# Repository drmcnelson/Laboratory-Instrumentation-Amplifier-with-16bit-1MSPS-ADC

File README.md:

# Laboratory Instrumentation Amplifier with bipolar inputs, 16bit 1MSPS ADC, SPI for Teensy, Arduino

By [Dr M. C. Nelson](https://github.com/drmcnelson/Laboratory-Instrumentation-Amplifier-with-16bit-1MSPS-ADC),  [Copyright 2020-2026](LICENSE)

> **Important Build Note:** To ensure performance and alignment with the validated hardware and firmware, please build only from the **[Original Repository](https://github.com/drmcnelson/Laboratory-Instrumentation-Amplifier-with-16bit-1MSPS-ADC)**. 
>
>  For technical assistance or commercial inquiries, please contact me. I do my best to answer emails as volume allows.
<br>

---
### Table of contents
[Introduction](#intro)<br>
[1. Contents and instructions](#repo)<br>
[2. Design details](#design)<br>
[3. Spice model](#spice)<br>
[4. ADC sampling and timing](#timing)<br>
[5. Detailed part selection](#parts)<br>
[6. PCBWay sponsorship and acknowledgement](#ack)<br>

---
<br>

## Introduction

Instrumentation amplifiers ("INAs") are important for making sensitive precise stable voltage measurements with very high input impedance and strong noise rejection.
If you do research in the physical sciences or engineering or study electrical phenomena in biological systems, then you have probably used an INA.
They are a cornerstone of traditional instruments such as electrometers, and EKG machines, and laboratory studies in chemical physics, semiconductors, advanced materials, organo- and bio- electronics.

But, if you have used a traditional INA in your research, you may have noticed that they have certain limitations (which we are going to address in this design).
In particular, there is a well known trade-off where precision or sensitivity comes at the expense of some combination of bandwidth and impedance.
INAs are typically low bandwidth devices.
But there are interesting phenomena, for example involving charge processes on microsecond time scales, where high impedance measurements with a fast INA would be an especially useful tool.

This limitation in traditional INAs arises, at least in part, in two properties of amplifier chips; the input voltage noise density e<sub>n</sub> (V/√Hz) and the input current noise density i<sub>n</sub> (A/√Hz).
At a given bandwidth and impedance these contribute to the noise as *v*<sub>e,rms</sub> ≈ e<sub>n</sub>√f and *v*<sub>i,rms</sub> ≈ z<sub>n</sub> i<sub>n</sub> √f.
Note that both have a factor of root frequency but the current noise density is also multiplied by impedance.
We can think of a "noise resistance", R<sub>n</sub> = e<sub>n</sub>/i<sub>n</sub>.
When the amplifier input sees an impedance larger than R<sub>n</sub>, current noise dominates and noise increases more rapidly with bandwidth.
Low noise with high impedance and bandwidth requires low noise density with high noise resistance, alongside adequate bandwidth and slew.

Let's illustrate this with a numerical example. If we want 16 bit data for a signal of 1V, the noise (rms) should be around 10μV or smaller.
For a bandwidth of 1MHz, we need e<sub>n</sub> ≈ 10nV/√Hz.
And for an impedance of 10Mohm, we need i<sub>n</sub>  ≈ 1fA/√Hz.
That is, we need current noise density in the range of single digit fA/√Hz, or smaller.
It is challenging to find what we need in older INA chips (see [Table 5.8 in H&H AOE 3rd ed.](https://archive.org/details/the-art-of-electronics-3rd-ed-2015_202008/page/363/mode/1up)),
But there *are* newer Op Amps with ~10nV/√Hz and ~1fA/√Hz noise densities, >MHZ bandwidth and >10V/μs slew.
So, this is where a "roll your own" approach can be an advantage over older INA chips.

Another issue in traditional INAs is that they most often have single ended outputs.
The modern paradigm in high performance analog to digital converters (ADC) is increasingly to have differential inputs.
And, there is a large repertoire of high performance fully differential amplifiers (FDA) designed specifically to drive these differential ADCs.
Rather than run a single ended BNC across the lab to an analog input in a crate, nowadays we interface our high performance analog circuit over a short differential path to a high performance ADC co-located on the same board and export an all digital interface to an inexpensive microcontroller board or a computer.
The analog noise is well managed within a small area of the circuit board, and an all differential signal path helps control noise all the way to the ADC with its digital interface.

### About the INA and other contents of this repository:

In this repository we provide cad files and software source codes to make and operate an up-to-date instrumentation amplifier (INA) that can accommodate 10Mohm impedances with 16 bit precision at 1MSPS.
The host interface is a simple convert (CNVST) signal and SPI.
Asserting the "CNVST" line initiates conversion to digital and
after 700 nsecs, with CNVST low, a 16 bit SPI transfer retrieves the data.
The logic level for the SPI and CNVST are per the Vdd pin in the external connector and can be between 1.7V to 5.5V.
The SPI can be clocked as fast as 100MHz.
The INA board must be powered at -5V and +5V.
We provide a dual power supply for this, which we describe later.

We include an Arduino "sketch" (as source code) to operate the INA from a Teensy or Arduino microcontroller (MCU) board, and a Python program to provide an interactive interface to operate the instrument and record and display data in real time from a desktop or laptop computer.
The MCU board appears as a serial device to the computer with human readable commands and responses.
The source code has been compiled for and run on a Teensy 4, an Arduino UNO R4 and a STM32 Nucleo 144 (F7).
We prefer the Teensy for having the best SPI implementation and the fastest USB.

As described below, the basic operation of the device is simple and it should be easy to customize or crib from the source code or python code to integrate the INA into your experiment.

In the following we include some discussion of the design process, especially as related to part selection.
And we provide spice models that may help you check your changes, if you want to make any changes to the design.

For a more thorough discussion of the electrical topics mentioned here, the reader is referred to Horowitz, P., & Hill, W. (2015). The art of electronics (3rd ed.). Cambridge University Press. ISBN-10 0521809266.  Especially see Chapter 5 "Precision Circuits" and Chapter 8 "Low Noise Techniques".

### A word on the Spi Instrumentation Project:

Building instruments is an old tradition in science.  Many of the great advances were by scientists working with instrument makers or who were themselves great instrument makers.  In recent decades there is a different kind of pressure on academic science.  There seems to be less time or interest for learning those kinds of skills, compared to writing proposals to buy equipment.
Consequently doing science has become much more expensive and the sort of science someone gets to do increasingly becomes a function of where they are.
But like many things in nature, science is cyclic, and scientists are resourceful.
With the advent of low cost high performance MCU boards, 3-d printers and low cost CNC machines, there is now a growing community in DIY lab equipment.
But, there is still a roadblock when it comes to some of the more advanced design challenges.
Few are able to build a photon tagging system with picosecond timing from scratch, for example.
Our contribution, as long time instrumentation physicists is to fill in the gap to make higher end capabilities available to this new paradigm.
We believe that combining high end instrumentation circuits with the new generation in Arduino type MCU boards can be a powerful tool that can bring important capabilities to your lab and contribute to truly open science.

There is a sponsor button at the top of this repository.  Please do consider joining with us and contributing to our effort.

### Our sponsor for the INA - [PCBWay](https://www.pcbway.com/) 

We want to express special appreciation to PCBWay for sponsoring assembly of the first INA boards.  I enjoyed working them and we plan to work with PCBWay going forward.  Going back to PCBWay for the next designs and contributing to their community project forum, really is the best kind of praise that I can muster for any vendor.

On that note, we plan to post this design to the PCBWay community forum as our first experiment in this paradigm.  We are eager to see how it works out.

### Obtaining boards:

To obtain boards, the options include ordering a board through PCBWay per the above, or contact me and then click the sponsor button.
The parts cost at Digikey is USD 36 per board at this writing.
Preparing an order still takes a few hours of careful attention since we review everything and check for updates in the BOM each time.
<br>

<br>

---

## 1. Contents and Instructions:
In this repo you will find:
<ol type="a">
<li>
KiCad files - for a high performance INA with a 16 bit 1 MSPS ADC that can be used with a Teensy 4.x, UNO R4, Nucleo144 or other Arduino type MCU board.
</li>
<li>
Source code - to operate the INA with any of the above platforms to record voltages and waveforms in single, averaged, clocked or triggered data acquisition modes, implement a set of human readable commands and transfer data over USB.
</li>
<li>
Python code - class library and utility program that runs on a desktop or laptop to operate the INA-MCU, view data in realtime and save data to disk files.
</li>
<li>
SPICE models - in LTSpice for the complete circuit and including a model for the ADC.
</li>
</ol>

### a) Fabrication
In the KiCAD files directory you will find a zip file with gerbers, drill and placement files, and a BOM.  These are easily regenerated from the KiCAD files.  If you are not familiar with ordering PCBs or assembly, the support team at PCBWay will guide you through the process.  Alternatively, you can sponsor a fabrication run and get a board.  Contact me for more information about this.

### b) Controllers
You may want to use the INA with one of our controllers.
Please see our new [Teensy 4.0 based controller here (rev3)](https://github.com/drmcnelson/Instrumentation-Controller-T4.0-Rev3) 
and our [T4.1 based controller here](https://github.com/drmcnelson/SPI-Instrumentation-Controller-T4.1).
We recommend these over other Arduino type MCU boards because of (a) the faster processor, (b) faster USB, (c) native 16 bit transfer capability already built into the Teensy SPI library, and (d) managed power.

### c) Power requirements and recommended power supply
The INA requires a -5V,+5V power supply.
The repo for our [+/-5V instrument power supply is  here](https://github.com/drmcnelson/Dual-pos-neg-5V-Supply-from-USB-power)
The power architecture of the INA assumes the the board is powered by this power supply.
The power supply in turn is normally powered from the filtered +5V power connector provided on the controller although it can alternatively be powered directly from USB

### d) The complete setup with controller and recommended power supply.
The following shows a complete setup with the INA, T4 based controller and power supply.  Notice the power supply is powered by the +5V connector on the controller and then powers the INA.   The INA is connected to the controller by a 12 pin (2x6) ribbon cable.

Here we show the input connectors. The instrumentation amplifier can be used as a single ended or differential input.  Input impedance is jumper selected as will be discussed.

### e) Input range and bandwidth
The range at each side of the differential input is -4V to +4V.
Full scale for the differential signal is therefore 8V.
Spectral response is flat from DC.
There is a low pass filter with time constant at the Nyquist limit for the 1MHz sample rate.

### f) Increasing gain
Gain can be increased by adding the resistor Rg.
There is a thru-hole footprint for this part located between the input header and the first Op Amp chip.
The gain equation is G = 1/2 + 10K/Rg.
Rg = 100 will give you a gain of 100.5.
With a gain of 100, the full scale range on each side of the differential input is effectively 40mV and the full scale differential signal is 80mV.
Larger inputs will clip since the rails for the Op Amps are just a little past -4V and +4V.

### g) Jumpers, selecting input impedance
There are three pin jumpers adjacent to each side of the differential input.
These allow you to select a 10M or 100K shunt to ground.
With no jumper installed the input impedance is that of the non-inverting input of the Op Amp.
It is important to have some path to ground, whether it is through the shunt resistor or the sample, rather than leave the input to drift off to one of the rails.

### h) Thermistor and measurements with voltage divider
You might use the internal 100K shunt with an external 100K thermistor to make accurate temperature measurements, or with an external resistor to form a divider to look at larger voltages.

The setup with a thermistor would look like the following where Vin is a known constant voltage and the internal resistor is selected by the jumpers as described above.  The controller has a high precision voltage reference output that you can use for this.

The setup with a divider would look similar to the above, though the external resistance might be considerably larger.
If you use a divider to measure large voltages, be very careful that the resulting voltage at the divider is within 4V.

Keep in mind also that Johnson (thermal) noise density for a resistor is about 0.13√R in units of nV/√Hz.
For a 16 bit precision on ±4V, 1LSB corresponds to 122μV. 
For 1Mohm and 1MHz the Johnson noise is 130uV.
So a 10:1 divider using the internal 100K and a 900K external can be okay.
With larger resistors more bits are used up for noise.
<br>

### i) Specs
<table style="width:60%;margin-left:30px">

<th>
Specifications
</th>
<tr>
<td style="padding-left:1rem">
 Input range
</td>
<td>
±4V each (±8V differential)
</td>
</tr>

<tr>
<td style="padding-left:1rem">
Input Impedance
</td>
<td>
10M, 100K, 1T (open), 20pF
</td>
</tr>

<tr>
<td style="padding-left:1rem">
Sampling rate
</td>
<td>
1 MSPS
</td>
</tr>

<tr>
<td style="padding-left:1rem">
Precision
</td>
<td>
16 bit
</td>
</tr>

<tr>
<td style="padding-left:1rem">
Digital Noise
</td>
<td>
+/-1 LSB
</td>
</tr>

<tr>
<td style="padding-left:1rem">
External Interface
</td>
<td>
CNVST, SPI to 100MHz, VDD 1.7V to 5.5V
</td>
</tr>

<tr>
<td style="padding-left:1rem">
Analog Power
</td>
<td>
-5V, +5V
</td>
</tr>
</table>

<br>
<br>

---

## 2. Design details

### a) Architecture

The traditional INA architecture is shown in the following diagram.
The input stage is a pair of Op Amps tied together by the resistor network R1-Rg-R1. The second stage is a difference amplifier with single ended output.
The overall gain is G = (1 + 2R1/Rg)(R3/R2).
This is a well studied circuit, you can read about it
in the textbook by Horowitz and Hill cited in the introduction,
or at [Wikipedia](https://en.wikipedia.org/wiki/Instrumentation_amplifier)
or in the many vendor application notes on the subject.

<p align="center">

<br>
<caption>
INA in the traditional configuration has single ended output.
</caption>
</p>

The following circuit diagram shows the INA architecture that we want to use for our circuit.
The differential amplifier is replaced with a fully differential amplifier (FDA) and the output from the FDA is interfaced to the differential input of a high performance ADC.
The ADC communicates with the outside world, for example a Teensy board or Arduino, over SPI.

<p align="center">

<br>
<caption>
INA with differential output stage and differential ADC.
</caption>
</p>

### b) Component selection, in brief

For our Op Amp selection, key parameters include the input current noise density i<sub>n</sub>, input voltage noise density e<sub>n</sub>, slew rate, and power supply rejection ratio (PSRR) as follows:
<ul>
<li>
Voltage noise density should be in the range of nV/√Hz for 16 bit precision with 1MHz bandwidth.
</li>
<li>
Current noise density in the range of single digit fA/√Hz is a pre-requisite for 16 bit precision with order 10 Mohm input impedance and 1 MHz bandwidth.
</li>
<li>
Slew rate in the range of 10V/us or better is a requirement for being able to study phenomena that appear as steps or transients on a μs time scale.
</li>
<li>
Power supply rejection ratio above 60dB is a requirement for the Op Amp and for the FDA, with the recommended power supply.  This is discussed later in further detail for the ADC.
</li>
</ul>

For the design provided here, the input stage is an ADA4510-2,  which is a dual Op Amp with i<sub>n</sub> = 4fA/√Hz, e<sub>n</sub> ≈ 5nV/√Hz, maximum slew = 19V/μs and PSRR 140dB.
As noted above, at 10Mohms at 1MHz, our noise is 40uV.

For the FDA, all of the above are important except that the current noise requirement is relaxed since the FDA sees low source impedances in the outputs from the first stage.  We choose an LT1994, which exceeds the front end specs with e<sub>n</sub> ≈ 3nV/√Hz and slew at 85V/μs.  Its PSRR is 105dB.

Both the ADA4510 and LT1994 are rail to rail parts.

For the ADC, our requirements include 16bits, 1MSPS, differential inputs, reference voltage, input range to 4V on each side of the differential input, SPI for the interface to the MCU, and it should accommodate 3.3V or 5V logic levels to be able to interface to a wide range of Arduino boards.  The precision and speed puts us in the range of a SAR type ADC.
The flexibility in logic levels narrows the selection somewhat.
It is also important to closely check performance specs including latency, missing codes, SNR, INL and DNL.

In this design we choose the Microchip MCP33131D as a 16 bit differential input 1MSPS SAR type ADC with SPI that can accommodate the required logic levels.
The SNR is listed as 91.3 dB which translates to a noise level of about 1 LSB.
This is one spec where the corresponding TI part might seem marginally better, but it comes at the cost of only accepting 3.3V logic.

For a voltage reference we select the REF3440 which has 3.8uV/V noise, low dropout at 100mV and is recommended for 16bit to 18bit ADCs.

### c) Interfacing to the ADC

SAR type ADCs, like most analog input architectures, feature a switched sampling capacitor.
A simplified version is as follows.
The switch closes connecting the input to the sampling capacitor.
The resistor represents the overall resistance inside the input including the closed resistance of the switch.
The capacitor then charges to the voltage at the input.
The switch opens and the SAR reads the voltage and converts it to a digital representation.

There are two interrelated challenges in driving a switched capacitor network; providing a charge reservoir for the in-rush current when the switch closes, and assuring that the capacitor charges quickly enough or that there is sufficient time in the sampling window, for the sampling capacitor to come within 1 LSB of the input voltage.
The recommended strategy is to provide a charge reservoir in the form of an external capacitor, and a buffer amplifier to charge the reservoir, as follows.

The trick in the above, is that these two capacitors charge on different time scales.
The sampling time allowed for charging the internal sampling capacitor is usually smaller than the period between samples.
The buffer has to supply current on the slower time scale to keep the reservoir charged, but it is the reservoir that absorbs the large fast spike when the switch closes.
   
The design process for the interface to the ADC is then:
   1) Choose the external capacitor to be a few times larger than the internal capacitor, then
   2) Choose the external resistor so that the time constant is faster than 1/2 of the sampling rate, and then
   3) Choose an Op Amp that is (a) able to deliver current equal to the full scale voltage divided by the external resistor, and (b) has a maximum slew that is much larger than the full scale voltage divided by the sampling period.
 
 With that high level view, let's take a look at our ADC.

The datasheet for the MCP33131D ADC provides the following equivalent circuit for its input.

Here we see a switched capacitor network for each side of the differential input.
There seems to be a novelty in that the sampling circuit is represented with a second switch to isolate the capacitor between samples.
Manufacturers often describe the state of the sampling capacitor as "unknown" between sampling events.
Here the intent seems to be a little more specific.
But in actuality there has to be some loss of charge between sampling events even if very small.

In practice, when you model a switched sampling capacitor network in SPICE, you always include a second switch to discharge the capacitor between samples.
If your driving circuit will get the sampling cap to the right voltage within the sampling window coming from 0 each time, it should be okay when you deploy it in the actual device.

Meanwhile, we have some important takeaways from the equivalent circuit.
The capacitor sees a time constant of 6.2 nanoseconds provided there is minimal impedance seen in the driving circuit, and we need something much larger than 30pf in the external capacitor.

---

## 3. SPICE model

For purposes of designing and modeling a circuit to drive an ADC, standard practice as mentioned above, is to use a model similar to the following for the switched sampling capacitor network:

In other words for purposes of modeling the sampling input, we discharge the capacitor between samples. 
A circuit that can drive the sampling cap from 0 to within 1LSB of the input voltage within the sampling period, should be sufficient for any reasonable state of the cap in operation.

The following shows our INA circuit with the equivalent circuit for the sampling input from the datasheet for the ADC.
External to the ADC, on each of the inputs, we have a resistor and capacitor to act as a charge reservoir for the sampling capacitor.
Internal to the ADC sample and hold, we have the switches as shown in the equivalent circuit from the datasheet.
Recall that this ADC isolates the capacitor between sampling windows.

<figure>
<p align="center">

<br>
<caption>
INA circuit model for SPICE,
</caption>
</p>
</figure>

The following shows (a) the voltages at the positive and negative inputs of the two front end amplifiers in two shades of green, and (b) the voltages at the two outputs of the FDA in two shades of blue.
As required for the ADC, the inputs are transformed from a bipolar range from -4V to +4V, to a unipolar range from 0V to 4V.

<p align="center">

<br>
<caption>
Voltages at inputs to the front end (green) and at the output
s of the FDA (red and lavender).
</caption>
</p>

The following shows (a) the output from one side of the FDA (blue), (b) the voltage on the sampling capacitor (red), (c) switching clock for the sampling network (grey).
We see that voltage on the sampling capacitor easily tracks the input to the ADC.

<figure>

<br>
<figcaption>
Positive side output from the FDA (blue), voltage on the sampling capacitor (red), and sampling clock (grey).
</figcaption>
</figure>

Here we add traces for the current through the sampling cap (green) and the capacitor services as the external charge reservoir (gold).
Notice the current spike through the sampling capacitor.
We see this is supplied by the external capacitor acting as charge reservoir, which slowly charges between switch events.
Notice also that there is no discernible spike in the output from the FDA.
So the charge reservoir is working as it is supposed.
On each sampling cycle, the sampling capacitor is able to rapidly come to the voltage presented at the input.

<figure>

<br>
<figcaption>
Positive side output from the FDA (blue), voltage on the sampling capacitor (red), current through the sampling capacitor (green), current through the external reservoir capacitor (gold) and the sampling clock (grey).
</figcaption>
</figure>

It is good practice to always check your ADC designs this way.  Find the equivalent circuit in the datasheet and implement it in terms of the capacitances and resistances and make sure you are driving it correctly.

Now, we have two more very important aspects of our circuit design to check, spectral response and noise.
We will look at these at the input to the ADC.
For completeness the following is our SPICE model modified for these analyses with large source impedance on each side of the differential input.

<figure>

<figcaption align="center">
Spice model with large source impedances.
</figcaption>
</figure>

The following shows the spectral analysis.  If you do not know how to do this in LTSpice, there is [a short tutorial video here](https://youtu.be/fziUQaVQxA4?feature=shared)
Here we see that our response is flat to 100kHz and then rolls off only slowly reaching -1.4dB and a 45 degree phase shift at around 1MHz.
If you want a more aggressive roll off you can substitute the caps in the feedback networks in the front end, or use larger caps for the charge reservoir in front of the ADC.

<figure>

<figcaption align="center">
Spectral response.
</figcaption>
</figure>

The following shows the noise analysis. As above, you can [see how to do this in LTSpice in the short tutorial video here](https://youtu.be/hBsBl27etYs?feature=shared).
https://youtu.be/hBsBl27etYs?feature=shared
 The noise density remains well below our target for 16 bit precision throughout the entire spectral range, even with a 1M source impedance at the input.

<figure>

<figcaption align="center">
Noise density.
</figcaption>
</figure>

So, it appears that the design meets our goals,  We expect to be able to make 16 bit 1MSPS measurements with high source impedance.
Spectral response is flat and then rolls off by less than 2dB above 100KHz and noise is under our 120uV requirement throughout the spectral range.

---

## 4. ADC Sampling and Timing

Voltage sampling is controlled by the CNVST pin in the double row header.  Assertion of this pin effectively marks the end of the sampling interval, causes the most recent level at the input to be converted to digital and made available for retrieval by the host.  The timing relationship between CNVST and the sampling window is important if the ADC sampling is to be synchronized to another instrument or specific external events.

The ADC, a MCP33131D-10, is described in detail in the datasheet found [here](https://ww1.microchip.com/downloads/en/DeviceDoc/MCP33131D-Data-Sheet-DS20005947B.pdf).
Figure 6-10, page 37, reproduced below, provides a high level view of the sampling, conversion and transfer cycle.  For detailed timing information see Figure 1-1, page 9 and related text.

In the diagram we see that when the CNVST pin is asserted, the inputs are latched and the ADC begins converting the latched signal, which represents the most 300nsecs at the inputs.  After  700nsecs conversion is complete and the data can be read over SPI by a 16 bit transfer.  The transfer can be shortened by asserting the CNVST pin again before the transfer is complete.  The maximum sample rate is 1MSPS for 16 bit with a 60MHz SPI or 800KSPS with a 30MHz SPI.
The data is a 2's complement 16 bit integer. It is easily converted to an unsigned 16 bit integer by toggling the high order bit.

---

## 5. Part selection in more detail

In this section we discuss one of the more important design choices, the input range, and then take a more detailed look at electrical characteristics and part selection.
This may be helpful if you want to modify the design.
Over-designing can present compromises and limitations just as under designing might.
If your requirements are sufficiently different from ours, the part selection process might lead you to a choice that is better for you.

Let's begin.

### a) Choosing the operating range

If we had a specific research goal in mind, we would consider the phenomena we are going to study, set the voltage range accordingly and proceed with the design from there.
Designing for a general case with a spec that reads "I want to use this for anything", is always far more difficult and laden with ambiguities.  A practical spec might be "what is the best we can do?"

As it turns out, 4V can be a convenient range with 5V as the primary power source.
For scientific applications, it is preferable to have a bipolar input, for example -4V to 4V rather than unipolar from 0 to 4V.
If I want to report a measurement as yielding zero volts (0V), most often I have to be able to read voltages above and below 0V.
And, if I want to study a phenomenon over a range that spans 0V, i.e. from negative to positive, then most often I want to do that all in one go, not half at a time.

As described earlier, for an INA any reasonable range is not  very constraining.
We can increase gain to zoom-in to a smaller range or add a series resistor to zoom-out to a larger range.
The bipolar choice has a more significant effect in that any unipolar measurement is inherently half-scale.

### b) What noise level do we need to achieve?

Given that we have chosen 16 bit precision, our noise level should be not very much larger than 1 part in 2<sup>16</sup> (1LSB) relative to our full scale input.
The ADC will have 1LSB of noise almost no matter what we do, because that's the physics of digitizing something.
Taking 4V as full scale our noise goal is 4V/65535 ~ 61μV at the input to the ADC, or 120μV at the input to the INA.

### c) Input voltage and current noise densities and the impedance bandwidth tradeoff.

As we discussed in the introduction, noise at the input to an Op Amp is described in terms of (a) its input voltage noise density e<sub>n</sub> (V/√Hz)
and (b) its input current noise density i<sub>n</sub> (A/√Hz).
We discussed this in the introduction.

Let's see how this works for the ADA4510.  This is an Op Amp designed for high precision and high input impedance.
The datasheet (Rev 0 is dated 7/2023), lists e<sub>n</sub> ~ 5nV/√Hz and i<sub>n</sub> ~ 4fA/√Hz.
With current noise density in the range of single digit fA/√Hz, our impedance threshold for current noise is 1Mohm,
But the noise is still small.
At 10Mohm and 1MSPS we are still doing well relative to our noise requirement for 16 bit measurements.

For comparison, the popular INA chip, the LT1167 (RevB datasheet dated 2011) has e<sub>n</sub> ~ 7.5nV/√Hz and i<sub>n</sub> ~ 60fA/√Hz above 100Hz.
That puts the impedance threshold at about 100Kohm.
For a large source impedance the LT1167 has to give away a lot of bandwidth compared to what we might expect with a well designed front end based on the ADA4510.

### d) Maximum slew rate and bandwidth

For an Op Amp, speed can be described by its bandwidth or gain bandwidth product (GBP) and by its maximum slew (V/μs)
It is possible to have a very large bandwidth, but be limited by the maximum slew.
For example, the LT1167, can support a gain of 1 with a 1MHZ bandwidth, but its maximum slew is 1.2V/μs.
The ADA4510 has a 10MHz gain bandwidth product, and its maximum slew rate is 19V/μs.
They both seem to have better than 1/2MHz bandwidth, but the ADA4510 can actually slew a full range (-4V to 4V) signal at that speed.

### e) Input capacitance

Looking again at the input characteristics, we might notice that there are two capacitances listed, C<sub>INDM</sub> the differential mode capacitance, and C<sub>INCM</sub> the common mode capacitance.a
The following diagram explains the terminology.
You can think of these quantities as the capacitances between the input pins and between each pin and its rail (or AC ground as shown).

We will mention here that the ADA4510 we have C<sub>INDM</sub> 20pF and  C<sub>INDM</sub> = 2pF, and the LT1167 has C<sub>INDM</sub> 1.6pF and  C<sub>INDM</sub> = 1.6pF.
But the situation is a little more complicated.
The best way to see what is going on is to run a spice model for the spectral response.
We will show that in a moment.

N.B. When impedances are large, small capacitances become even more important.  Pay careful attention to recommendations in the datasheets about layout around input pins for all of the active parts in the design.

### f) Power supply rejection ratio.

Almost any active part used in an analog circuit has a power supply rejection ratio PSRR listed in its datasheet.
The name of the game, is that the PSRR for each part involved in the analog chain acting on the the noise level of whatever is powering it, has to be better than the noise level that we are trying to achieve in our design.   For a 16 bit board, we need an SNR better than 96dB.

The recommended power supply is posted [here](https://github.com/drmcnelson/Dual-pos-neg-5V-Supply-from-USB-power).
This is based on the LT1930 and LT1930, the datasheets indicate output noise of about 1mV.   For our amplifier chips a PSRR of even 60dB will get us into the μV range that we need for our noise specs. PSRR for the ADA4510 is 140dB, so we're in pretty good shape.
Our FDA an LT1994 has a PSRR of 105dB.  We're still good.

The ADC is an MCP33131D and is powered from a 1.8V LDO TPS72218 with noise level 90μV.
A PSRR at -20dB reduces to 9μV or less than 1LSB in the digital output, and vref is a REF3440 with noise level 3.8μV/V or 16μV, again significantly less than 1LSB.

### g) On rail to rail amplifiers

Our 4V range means that we need an Op Amp and FDA that are rail-to-rail with regard to both inputs and outputs and with a common mode that goes to at least 1/2 of the rail.

Some R-R are more R-R than others.
It is important to check the datasheet carefully to make sure the part you are selecting has adequate input, output and common mode ranges.
Traditional INA are generally not R-R.

Our ADA4510 does go right to the rails (from 0.15V above Vs- all the way to Vs+). 
The LT1994 is also rail to rail in terms of inputs and outputs but its common mode level has to be at least 1 volt from either rail.
That is okay for our case.  We are using the common mode control pin and setting it to the midpoint of the two rails.

---

## 6. Acknowledgement

### Our sponsor - [PCBWay](https://www.pcbway.com/) 

We want to express special appreciation to PCBWay for sponsoring assembly of the first INA boards.  The work product and materials are quite good, and the staff were helpful way above and beyond expectations.  I look forward to working with PCBWay again.

Going back to PCBWay for the next designs and contributing to their community project forum, really is the best kind of praise that I can muster for any vendor.

On that note, we plan to post this design to the PCBWay community forum as our first experiment in this paradigm.  We are eager to see how it works out.

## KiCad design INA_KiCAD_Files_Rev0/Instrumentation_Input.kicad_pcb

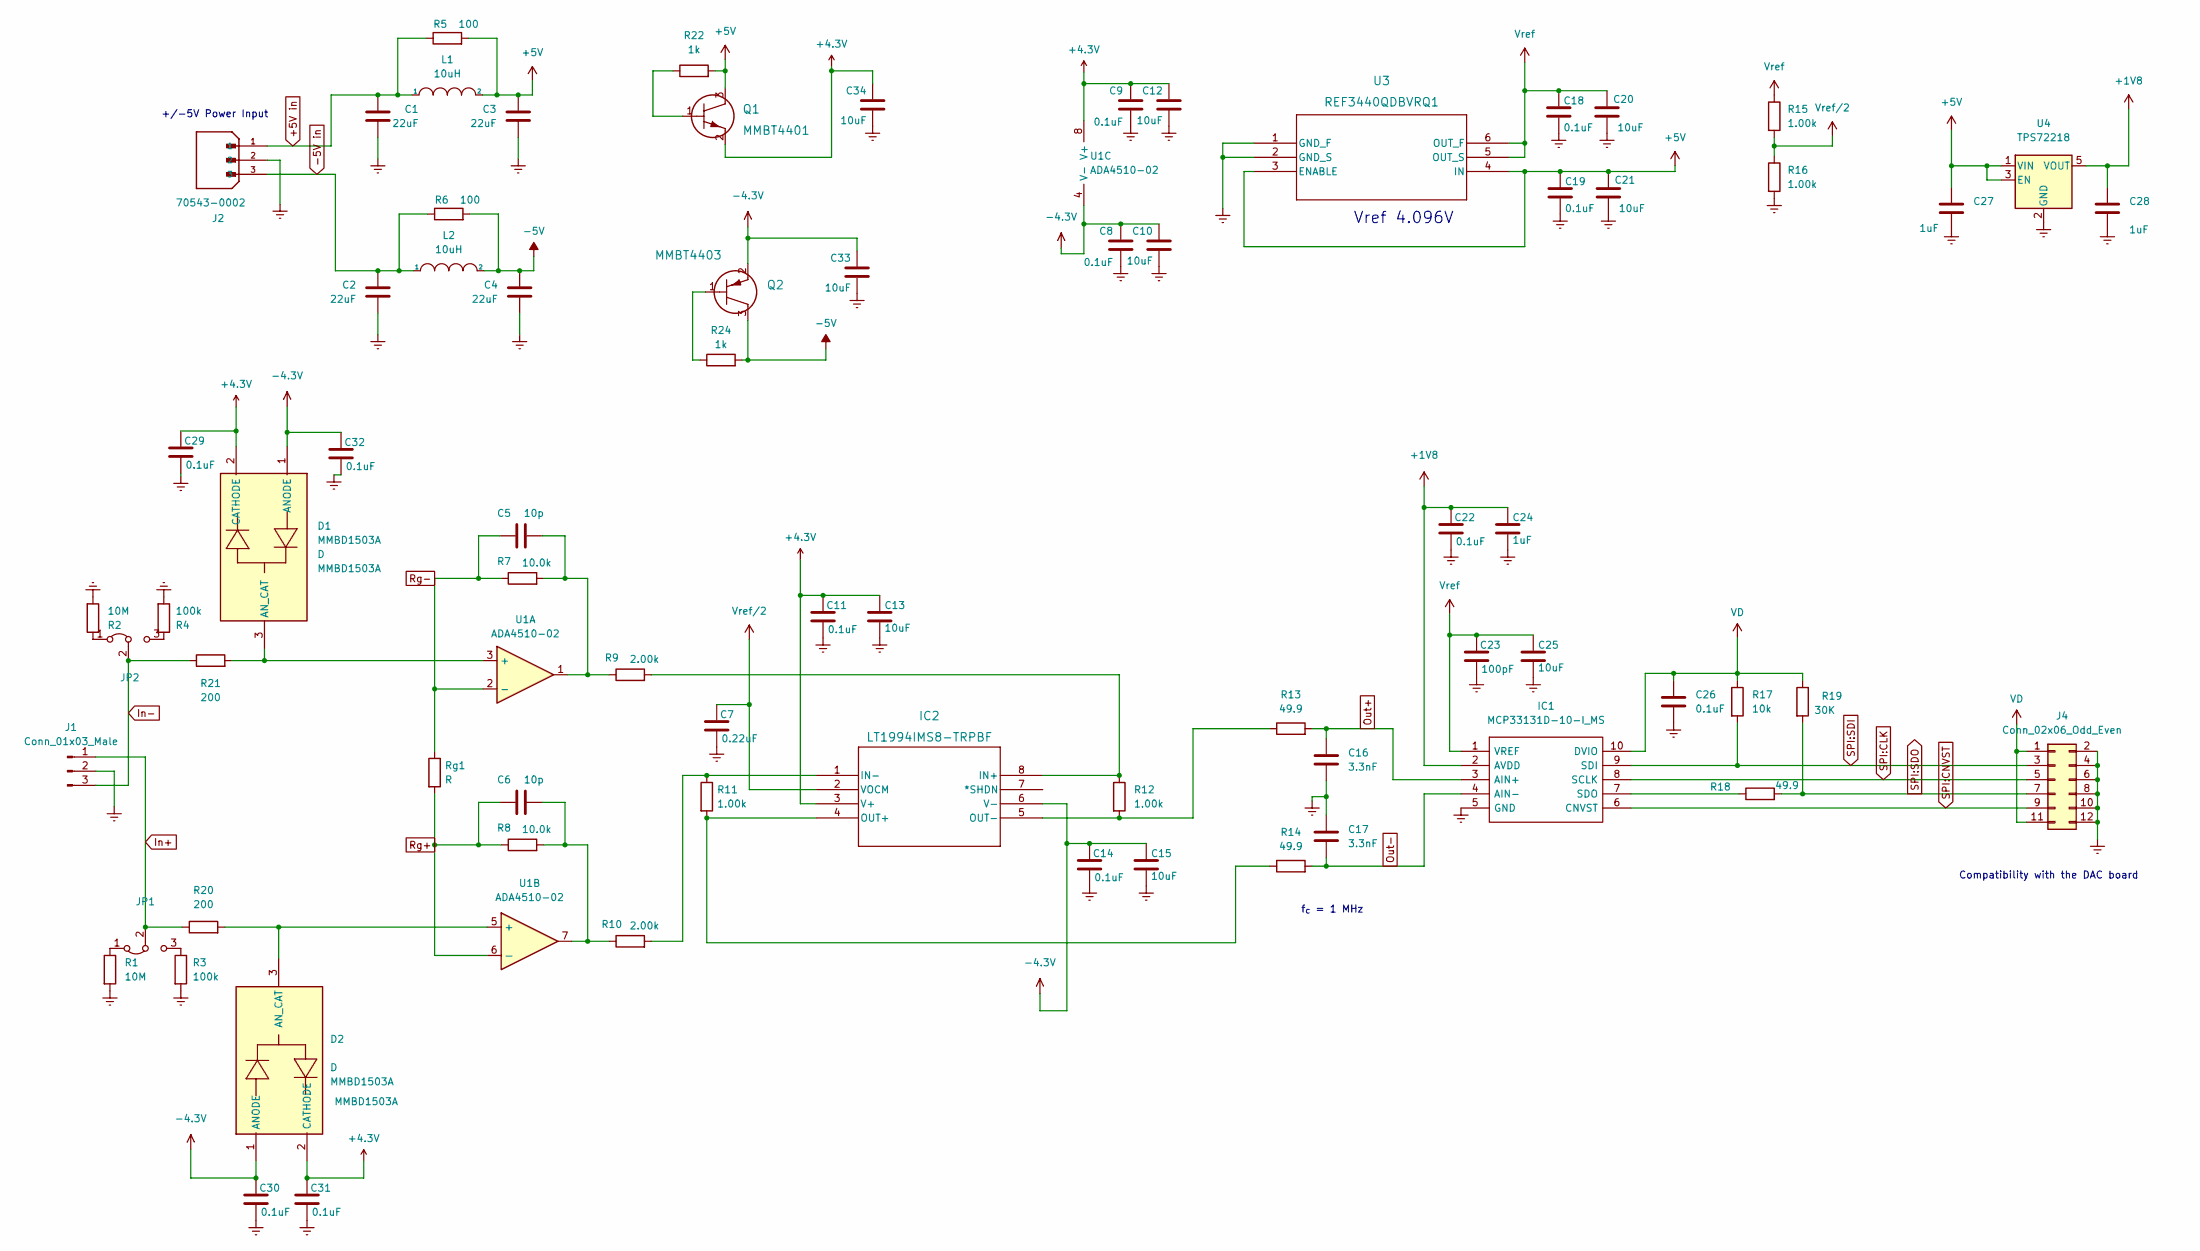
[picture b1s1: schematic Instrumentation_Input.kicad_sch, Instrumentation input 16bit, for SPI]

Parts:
C1, C2, C3, C4: 22uF; C_0805_2012Metric; Digikey 490-12389-1-ND
C5, C6: 10p; C_0402_1005Metric; Digikey 478-KAQ05ACG1H100FHCT-ND
C7: 0.22uF; C_0402_1005Metric; Digikey 490-10671-1-ND
C8, C9, C11, C14, C18, C19, C22, C26, C29, C30, C31, C32: 0.1uF; C_0402_1005Metric; Digikey 490-6328-1-ND
C10, C12, C13, C15, C20, C21, C25, C33, C34: 10uF; C_0603_1608Metric; Digikey 490-12317-1-ND
C16, C17: 3.3nF; C_0402_1005Metric; Digikey 490-GRM1555C1H332GE01DCT-ND
C23: 100pF; C_0402_1005Metric; Digikey 399-17546-1-ND
C24, C27, C28: 1uF; C_0402_1005Metric; Digikey 490-13339-1-ND
D1, D2: MMBD1503A; SOT-23; Mouser Part Number 512-MMBD1503A
IC1: MCP33131D-10-I_MS; MSOP-10_3x3mm_P0.5mm; Manufacturer_Part_Number MCP33131D-10-I/MS; Mouser Part Number 579-MCP33131D10IMS
IC2: LT1994IMS8-TRPBF; SOIC8_LT1994IMS8-TRPBF_ADI; Digikey 505-LT1994IMS8#PBF-ND
J1: Conn_01x03_Male; PinHeader_1x03_P2.54mm_Vertical; Digikey 3M156268-03-ND
J2: 70543-0002; MOLEX_70543-0002; PARTREV M1; Digikey WM4801-ND
J4: Conn_02x06_Odd_Even; PinHeader_2x06_P2.54mm_Vertical; Manufacturer_Part_Number 929665-02-06-I; Digikey 3M156308-12-ND
JP1, JP2: Conn_01x03_Male; PinHeader_1x03_P1.27mm_Vertical; Manufacturer_Part_Number GRPB031VWVN-RC; Digikey S9014E-03-ND
L1, L2: 10uH; L_Taiyo-Yuden_NR-40xx; Manufacturer_Part_Number 587-2886-1-ND; Digikey 587-2886-1-ND
Q1: MMBT4401; SOT-23_LTO; Digikey 4878-MMBT4401CT-ND
Q2: MMBT4403; SOT-23_LTO; Digikey 4878-MMBT4403CT-ND
R1, R2: 10M; R_0603_1608Metric_Pad0.98x0.95mm_HandSolder; Digikey RMCF0603FT10M0CT-ND
R3, R4: 100k; R_0603_1608Metric_Pad0.98x0.95mm_HandSolder; Digikey P100KHCT-ND
R5, R6: 100; R_0603_1608Metric; Digikey 541-2786-1-ND
R7, R8: 10.0k; R_0402_1005Metric; Digikey RNCF0402BTE10K0CT-ND
R9, R10: 2.00k; R_0402_1005Metric; Digikey 10-ERA-2VEB2001XCT-ND
R11, R12, R15, R16: 1.00k; R_0402_1005Metric; Digikey 738-RNCF0402BTE1K00CT-ND
R13, R14, R18: 49.9; R_0402_1005Metric; Digikey P49.9LCT-ND
R17: 10k; R_0402_1005Metric; Digikey P10.0KLCT-ND
R19: 30K; R_0402_1005Metric; Digikey P30.0KLCT-ND
R20, R21: 200; R_0402_1005Metric; Digikey P200LCT-ND
R22, R24: 1k; R_0402_1005Metric; Digikey P1.00KLCT-ND
Rg1: R; R_Axial_DIN0204_L3.6mm_D1.6mm_P5.08mm_Horizontal
U1: ADA4510-02; SOIC-8_3.9x4.9mm_P1.27mm; Manufacturer_Part_Number ADA4510-2ARZ; Digikey 505-ADA4510-2ARZ-RLCT-ND
U3: REF3440QDBVRQ1; SOT-23-6_TEX; Manufacturer_Part_Number REF3440QDBVRQ1; Digikey 296-53237-1-ND
U4: TPS72218; SOT-23-5; Manufacturer_Part_Number TPS72218DBV (R/T); Digikey 296-27048-1-ND

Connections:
+1V8: C22.1, C24.1, C28.1, IC1.2 (AVDD), U4.5 (VOUT)
+4.3V: C9.1, C11.1, C12.1, C13.1, C29.1, C31.1, C34.1, D1.2 (CATHODE), D2.2 (CATHODE), IC2.3 (V+), Q1.2, U1.8 (V+)
+5V: C3.1, C19.2, C21.1, C27.1, L1.2, Q1.3, R5.2, R22.2, U3.3 (ENABLE), U3.4 (IN), U4.1 (VIN), U4.3 (EN)
+5V in: C1.1, J2.1, L1.1, R5.1
-4.3V: C8.1, C10.1, C14.1, C15.1, C30.1, C32.1, C33.1, D1.1 (ANODE), D2.1 (ANODE), IC2.6 (V-), Q2.2, U1.4 (V-)
-5V: C4.1, L2.2, Q2.3, R6.2, R24.2
-5V in: C2.1, J2.3, L2.1, R6.1
Earth: C1.2, C2.2, C3.2, C4.2, C7.2, C8.2, C9.2, C10.2, C11.2, C12.2, C13.2, C14.2, C15.2, C16.2, C17.1, C18.1, C19.1, C20.2, C21.2, C22.2, C23.2, C24.2, C25.2, C26.2, C27.2, C28.2, C29.2, C30.2, C31.2, C32.2, C33.2, C34.2, IC1.5 (GND), J1.2, J2.2, J4.2, J4.4, J4.6, J4.8, J4.10, J4.12, R1.2, R2.2, R3.2, R4.2, R16.2, U3.1 (GND_F), U3.2 (GND_S), U4.2 (GND)
In+: J1.1, JP1.2 (C), R20.1
In-: J1.3, JP2.2 (C), R21.1
unnamed: C5.2, R7.2, R9.1, U1.1
unnamed: C6.2, R8.2, R10.1, U1.7
unnamed: D1.3 (AN_CAT), R21.2, U1.3 (+)
unnamed: D2.3 (AN_CAT), R20.2, U1.5 (+)
unnamed: IC1.7 (SDO), R18.1
unnamed: IC2.1 (IN-), R10.2, R11.1
unnamed: IC2.4 (OUT+), R11.2, R14.1
unnamed: IC2.5 (OUT-), R12.2, R13.1
unnamed: IC2.8 (IN+), R9.2, R12.1
unnamed: JP1.1 (A), R1.1
unnamed: JP1.3 (B), R3.1
unnamed: JP2.1 (A), R2.1
unnamed: JP2.3 (B), R4.1
unnamed: Q1.1, R22.1
unnamed: Q2.1, R24.1
Out+: C16.1, IC1.3 (AIN+), R13.2
Out-: C17.2, IC1.4 (AIN-), R14.2
Rg+: C6.1, R8.1, Rg1.2, U1.6 (-)
Rg-: C5.1, R7.1, Rg1.1, U1.2 (-)
SPI:CLK: IC1.8 (SCLK), J4.5
SPI:CNVST: IC1.6 (CNVST), J4.9
SPI:SDI: IC1.9 (SDI), J4.3, R17.2
SPI:SDO: J4.7, R18.2, R19.2
VD: C26.1, IC1.10 (DVIO), J4.1, J4.11, R17.1, R19.1
Vref: C18.2, C20.1, C23.1, C25.1, IC1.1 (VREF), R15.1, U3.5 (OUT_S), U3.6 (OUT_F)
Vref/2: C7.1, IC2.2 (VOCM), R15.2, R16.1

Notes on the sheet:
+/-5V Power Input
Vref 4.096V
Compatibility with the DAC board
f_{c} = 1 MHz

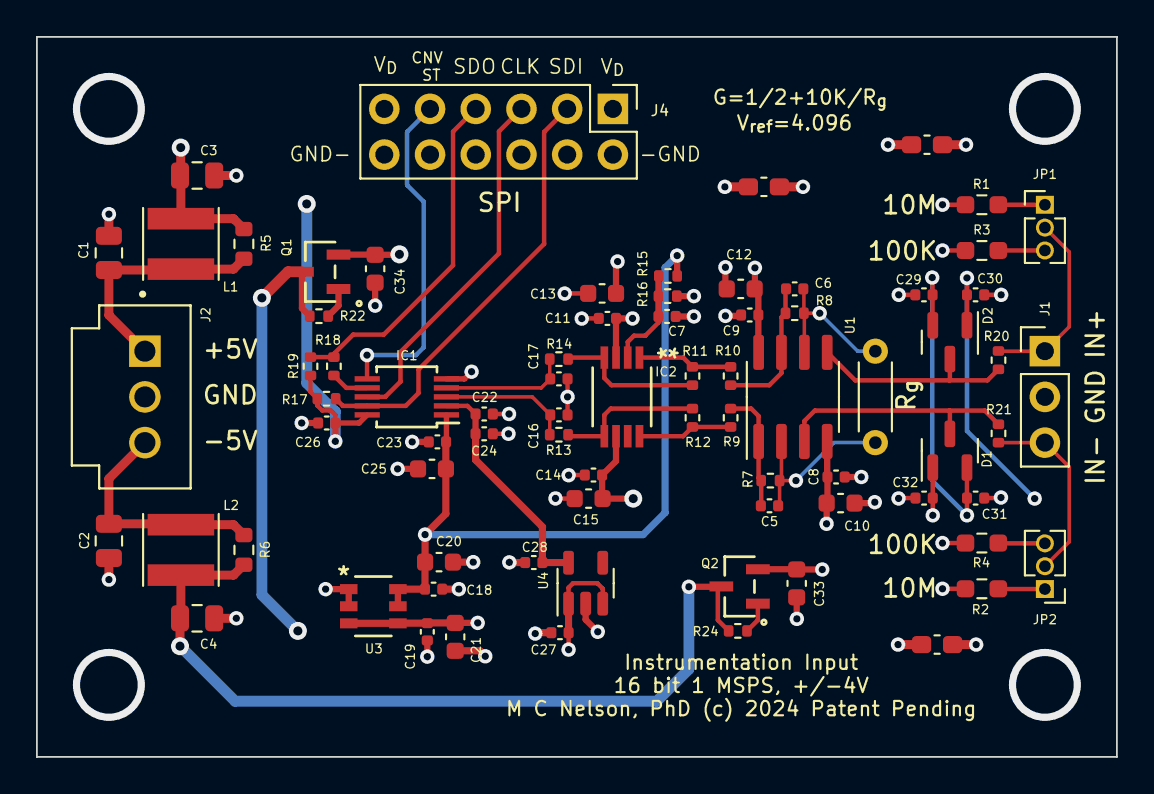
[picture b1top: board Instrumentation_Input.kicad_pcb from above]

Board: 4 copper layers, 60.0 x 40.0 mm, 74 parts (0 on the bottom side), 36 nets.

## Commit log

2025-01-30 Initial Readme upload
2025-01-30 Initial KiCAD upload
2025-01-30 Initial SPICE mode upload
2025-01-30 Initial sketch upload
2025-01-30 Initial SPICE model upload
2025-01-30 Initial Python upload
2025-01-30 Initial README
2025-01-30 Initial FAB files upload
2025-10-13 Pin assignment for R3 controller
2025-10-13 Fix overflow in averaged values.

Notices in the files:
INA_KiCAD_Files_Rev0/Instrumentation_Input.kicad_pcb:
M C Nelson, PhD (c) 2024 Patent Pending
INA_KiCAD_Files_Rev0/Instrumentation_Input.kicad_sch:
Mitchell C Nelson, PhD (c) 2024
